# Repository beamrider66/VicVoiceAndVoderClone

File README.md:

# VVVC — Vic Voice and Voder Clone

Speech firmware for **ESP32 boards**, with always-on GPIO PWM audio and an
optional **ES8388 Audio-Kit 16-bit I2S DAC and speaker amplifier**. The same
SC-01 speech and startup tones feed both outputs without selecting a mode.
An absent codec does not prevent a normal DevKit from starting and speaking
through its PWM pin. GPIO audio needs an external filter and amplifier.

## One combined interface

The VIC serial connection accepts English text, compact SC-01 phoneme blocks,
VIC-Voice escape controls and VIC-Voder `SET TTY LO` / `SET TTY HI` baud commands
together. Text and phonemes can be mixed within a line. There is no mode to
select, and the former USB `-mode` commands have been removed.

Both the VIC connection and the USB console also accept commands to learn
phrases in numbered **RAM-only slots**, then replay them by number. Slots are
shared between the connections and disappear when the ESP32 reboots or resets.

All speech uses **one Votrax SC-01 approximation**. Startup defaults are
2400 baud with echo on; escape controls can switch echo off or back on. Settings
are held in RAM and reset restores the defaults. The USB console runs at
**115200 baud**. All dash commands work on **both connections**, including
`-demo`, `-tone`, `-phonemes`, `-help` and every learning command. Replies return
to the connection that sent the command. `-demo` is a one-shot test and
preserves the serial settings and learned slots.

The combined interface provides VIC-Voice-style controls and **SC-01 compact
phone numbering**, plus the basic text and
baud commands documented in the [VIC-Voder user's guide](https://www.geocities.ws/cbm/vic-voder/vic-voder-manual.pdf).
It does not implement the original SP0256 phone set or reproduce VIC-Voder's
Festival voice or Linux features. Combining the controls also means command
handling and echo defaults differ from the individual original products.

## End-user guide

The combined [user and VIC-20 wiring guide](output/pdf/VVVC_User_and_VIC20_Wiring_Guide_v2.pdf)
contains USB and VIC BASIC examples, learning commands, the Wizard of Wor loader
and all 75 phrase numbers. Its wiring section labels the viewing direction and
TOP for the computer port, cable mating face and wire/solder side. It remains a
review draft until the physical VIC connection and examples have been tested.

To regenerate it from the project folder:

```sh
python -m pip install -r tools/requirements-docs.txt
python tools/build_user_guide.py
```

## KiCad VIC user-port carrier (draft)

The repository also contains a first-pass [ESP32 user-port/audio carrier](hardware/VVVC_UserPort_Audio_WIP/README.md).
It is designed for a 38-pin ESP32 DevKitC/WROOM powered from USB, with a
dual-gang volume wheel for the shared 3.5 mm and RCA outputs, user-port edge
contacts, and enclosure standoff holes. The PCB is still a placement/netlist
draft: the exact audio-buffer and connector parts must be selected, routing
completed, and the enclosure checked before fabrication. The flashing guide
continues to cover firmware installation and serial setup; it does not present
this unfinished carrier as a production hardware option.

## Build and upload

On Windows, double-click [`build_and_flash.bat`](build_and_flash.bat) to build
and flash **COM3**. The window stays open to show the result. From a terminal:

```bat
build_and_flash.bat COM3
build_and_flash.bat COM7
build_and_flash.bat --build-only
```

Use the board's USB-to-UART port, and close the serial console first. The script
finds PlatformIO in its usual VS Code installation or on PATH, builds the
`esp32dev` environment, and uploads only if the build succeeds. It works from
any current directory. Flashing resets the board and clears learned RAM phrases;
run the Wizard loader again if needed. `--build-only` leaves the board alone.

Open this folder in VS Code with PlatformIO, or run:

```sh
pio run
pio run -t upload
pio device monitor
```

The default build environment is `esp32dev`. The Espressif32 platform is pinned
to `7.0.1`, the pinned build version. PlatformIO
automatically downloads Phil Schatzmann's `arduino-audio-driver` at **v0.1.3**,
the same codec library version used by the firmware. No filesystem image, Wi-Fi
configuration or separately downloaded speech library is required.

The available builds use 4 MB flash layouts and the board's USB-to-UART port:

| Environment | Chip family | PWM audio GPIO | VIC RX / TX | Codec output |
| --- | --- | --- | --- | --- |
| `esp32dev` | Original ESP32 (Audio-Kit or DevKit) | 22 | 18 / 5, UART2 | ES8388 if detected |
| `esp32c3` | ESP32-C3 | 4 | 6 / 7, UART1 | None |
| `esp32s2` | ESP32-S2 | 4 | 6 / 7, UART1 | None |
| `esp32s3` | ESP32-S3 | 4 | 6 / 7, UART1 | None |

For example, `pio run -e esp32c3 -t upload --upload-port COM7`. The batch file
continues to build the original ESP32 target. Each chip family needs its own
binary; PWM does not make one binary run on every ESP32. These four families
are build-checked with the pinned Arduino 2.0.17 toolchain. C2/C6/H2/P4 and
other families are not supported by these builds. Boards need at least 4 MB
flash and the chosen pins exposed and unused. Native USB-only boards need a
USB-to-UART adapter for the console with these profiles.

The PWM pin can be changed with `-DVVVC_PWM_PIN=number` in the environment's
`build_flags`. Preserve existing flags. Avoid flash, PSRAM, USB, boot-strapping,
UART, onboard peripheral and codec pins. The classic ESP32 build probes I2C
on GPIO33/32; keep these free even on a board without the codec. Do not press
any board button connected to an output. Check the specific board schematic.

If PlatformIO is not on your Windows PATH, its installed executable on this
machine can be invoked from PowerShell:

```powershell
& "$env:USERPROFILE\.platformio\penv\Scripts\pio.exe" run
& "$env:USERPROFILE\.platformio\penv\Scripts\pio.exe" run -t upload
& "$env:USERPROFILE\.platformio\penv\Scripts\pio.exe" device monitor
```

If several boards are connected, specify the appropriate `--upload-port COMx`
or monitor `--port COMx`. The application image is
`.pio/build/esp32dev/firmware.bin`; use PlatformIO upload to include the matching
bootloader and partition table.

## Browser installer

The installer is published at <https://beamrider66.github.io/VicVoiceAndVoderClone/>.
The public project repository holds firmware source on `main` and generated
website files on `gh-pages`. To rebuild and publish an update:

```powershell
powershell -File tools/publish_pages.ps1
```

GitHub Pages serves the root of the project's `gh-pages` branch over HTTPS.
The script requires Python, PlatformIO, Git and authenticated push access to
`beamrider66/VicVoiceAndVoderClone`. It builds locally and pushes the static files;
GitHub then deploys them automatically.

**Direct browser flashing requires HTTPS** (with a trusted certificate), or a
local server on `http://localhost`. The installer provides a ZIP download:
extract it, run `start-local.bat` with Python 3 installed, then open
`http://localhost:8765` in desktop Chrome or Edge.

Build the flashing site locally with:

```powershell
python tools/build_web.py
```

Omit `--publish` to generate only `build/web`. The script builds the current
firmware, merges the four flash images with DIO/40 MHz/4 MB settings, packages
ESP Web Tools 10.4.0 locally (verified against its npm SHA-512), and creates a
manifest, firmware checksum, guide and portable ZIP. No CDN is needed at runtime.
Publishing verifies copied files and retains older firmware images. Source page
files are in `web/`; generated files are ignored under `build/`.

The installer selects ESP32, C3, S2 or S3 firmware by chip family. It cannot
identify board wiring; users must check the pins above. Installation resets learned RAM
slots. This packaging process does not flash a connected device.

## Wiring

Connect the speaker to the Audio-Kit's **labelled speaker terminals**. The
headphone output is enabled as well. This uses the documented ES8388
Audio-Kit pin layout (`AudioKitEs8388V1` in the driver), including the required
master clock. The internal board connections are:

| Codec / amplifier connection | ESP32 pin |
| --- | --- |
| I2C SCL / SDA | GPIO 32 / 33 |
| I2S master clock (MCLK) | GPIO 0 |
| I2S bit clock (BCLK) | GPIO 27 |
| I2S word clock (LRCLK) | GPIO 25 |
| I2S data to ES8388 | GPIO 26 |
| Speaker amplifier enable | GPIO 21 |

Audio is **44.1 kHz, signed 16-bit stereo**, preserving the full SC-01 PCM
sample values and the documented Audio-Kit playback timing. Startup volume
is **48%**, adjustable with `audioVolumePercent` in
[`include/config.h`](include/config.h). GPIO25 carries the codec's digital
word clock, not analog audio. Audio-Kit buttons, SD and audio capture are unused.

### Always-on GPIO audio

GPIO22 on the original ESP32 (GPIO4 on the C3/S2/S3 profiles) carries the same
mono PCM as the codec, converted to **8-bit PWM with a 156.25 kHz carrier**.
It continues to run when no codec is installed; there is no fallback mode or
audio selection command. The codec retains the full 16-bit samples. PWM volume
is independent of the codec's 48% volume setting; adjust the external amplifier.
The two outputs have independent buffering/clocks and are not phase-aligned.

Use this starting circuit into a high-impedance amplifier input (47 kOhm or
greater). Values may need adjustment for the amplifier and desired bandwidth:

```text
PWM GPIO -- 1k --+-- 4.7k --+-- 1uF film -- amplifier audio input
                |         |
               22nF      4.7nF
                |         |
ESP32 GND ------+---------+-------------- amplifier signal ground
```

The RC stages suppress the PWM carrier; the film capacitor blocks the roughly
1.65 V idle DC level. Keep wires short and start at low amplifier volume. Use
an amplifier to drive the speaker: **do not connect a speaker or headphones
directly to the GPIO**, and do not connect the GPIO to the Audio-Kit speaker
terminals. The pin is a 0–3.3 V PWM signal, not a built-in DAC output or a
digital interface for an external DAC. During idle/after BREAK it rests at
50% duty; the startup beep, `-tone`, `-demo` and every speech source use it.

PWM uses LEDC low-speed channel/timer 0 and hardware timer 0. Its ring buffer
is in internal RAM; the sample ISR does no allocation or logging. The timer
rate is about 44101.43 samples/s (33 ppm above the nominal 44100 Hz). A stopped
sample timer times out rather than hanging speech. A failed audio backend is
disabled while the other continues. This new GPIO path has host and build
checks but still needs physical filter, waveform and simultaneous audio tests.
The existing PDF covers the earlier Audio-Kit wiring, not this new GPIO circuit.

The VIC interface retains its existing wiring:

| Connection | ESP32 pin |
| --- | --- |
| VIC user-port M, transmitted data, through a 5 V to 3.3 V divider | GPIO 18, UART2 RX |
| VIC user-port B and C, received data / receive interrupt | GPIO 5, UART2 TX, connected to both |
| VIC user-port A or N, signal ground | GND |

Use the documented interface circuitry. For the RX divider, the firmware
uses 10 kOhm from user-port M to GPIO 18 and 18 kOhm from GPIO 18 to ground.
Connect grounds and power the ESP32 separately over USB. This is a TTL
user-port connection, not the round IEC bus or a PC's RS-232 voltage interface.
Do not connect the VIC's 5 V transmit signal directly to the ESP32.

GPIO 18 and 5 are shared with Audio-Kit keys 5 and 6; leave those keys unused
when the VIC interface is connected. Startup echo, buffer sizes, phrase-bank
limits and the line timeout can also be changed in `include/config.h`.

## First test

After upload, open the USB console at 115200 baud with a newline terminator.
Startup plays the original **880 Hz then 440 Hz** audio test (300 ms each,
with a 100 ms gap) through PWM and any detected ES8388, then prints help. To check speech too, send:

```text
-demo
```

Expect 880 Hz and 440 Hz tones, then “HELLO WORLD. THIS IS VIC VOICE.” and
“GET READY.” The last phrase exercises direct phoneme synthesis separately
from English conversion. The console prints `Demo complete.` on success.
The demo checks the local speech/audio path; a VIC BASIC test checks the wiring
and UART separately.

If codec or I2S initialization fails, the console reports the error and skips
the startup tones. Check the board, then reset the ESP32. Learning and help
commands remain available, but playback reports failure while audio is
unavailable. Normal speech drains its final samples before returning; BREAK
clears queued audio immediately.

Commands accepted over USB or the VIC serial connection:

```text
HELLO WORLD
-phonemes G EH T R EH D Y PA1
-phonemes I0_AH I1_AH I2_AH I3_AH
-tone
-help
```

With VIC channel 1 already open at 2400 baud, the same commands can be sent with
`PRINT#1`, for example:

```basic
PRINT#1,"-DEMO"
PRINT#1,"-TONE"
PRINT#1,"-PHONEMES G EH T R EH D Y PA1"
PRINT#1,"-HELP"
```

Send one at a time and wait for completion. Demo and tone reply with
`Demo complete.` and `Tone complete.`; direct phonemes reply with
`OK PHONEMES`. Errors also return to the requesting connection. Replies use
ASCII and CR/LF. Disable VIC echo before parsing replies (see below), and
read `-help`/`-slots` output as it arrives: long replies can exceed the VIC's
small receive buffer. Explicit demo, tone and phoneme commands still play
audio with PSEND enabled. Unknown dash commands report an error on either port.

On the USB console, a leading `~`, PETSCII
pi (`0xDE` or `0xFF`) or UTF-8 pi selects **compact** Type 'N Talk bytes for that
USB line. Use `-phonemes` for readable SC-01 tokens. USB lines accept up to 253
bytes; longer lines are discarded with an error, rather than spoken partially.
USB commands run between utterances. There is no background demo loop.

## Learning and recalling phrases

There are **80 slots, numbered 1 through 80**, each holding up to **256 SC-01
phonemes**. Text is converted when learned; recall uses the saved phonemes
directly. Named phonemes retain `I0_` through `I3_` inflection prefixes. All
storage is normal RAM, using about 20 KB for the bank plus conversion workspace.
The firmware does not save phrases to flash or a filesystem.

Send these commands as complete CR- or LF-terminated lines on either port:

| Command | Action |
| --- | --- |
| `-learn 1 text HELLO WORLD` | Convert English and store it in slot 1, without speaking it |
| `-learn 2 phonemes G EH T R EH D Y PA1` | Store named SC-01 phonemes in slot 2 |
| `-learn 3 compact ~\{j~?` | Store compact codes for `G EH T PA1` in slot 3 |
| `-play 1` | Speak slot 1 |
| `-forget 1` | Delete slot 1 |
| `-slots` | List occupied slots and their phoneme counts |
| `-clear` | Delete every slot |

Commands and named phonemes are case-insensitive. Compact codes are
case-sensitive bytes, preserved exactly. In the compact example, `\` is one
literal backslash. A compact block must have an opening pi marker and a closing
`?`; its data bytes must all be `0x40` through `0x7F`. Use ASCII `~` or PETSCII pi
(`0xDE` / `0xFF`) on the VIC connection; the USB console also accepts UTF-8 pi.
The opening marker and closing `?` are not stored. Compact input uses inflection
zero; use named phonemes to specify inflection.

Relearning an occupied slot replaces it only after the complete new phrase
passes validation. Invalid or oversized input leaves the old phrase intact.
Text input is limited to 253 bytes before conversion, and the converted result
must fit in 256 phones. The USB line limit is 253 bytes **including the command**;
the VIC buffer accepts up to 768 bytes including the line terminator. The bank
limits can be changed with `phraseSlotCount` and `phrasePhoneLimit` in
`include/config.h`.

All dash commands require CR or LF. An unfinished VIC command is rejected at
the inactivity timeout or buffer limit; the remainder is discarded through
the next CR/LF. When a receive overflow occurs during playback, pending input
is discarded through the next terminator. This prevents a truncated learn
command from silently replacing a valid slot. Send one command and wait for
its reply before sending the next.

### Replies

Replies are ASCII, terminated by CR/LF, and sent to the connection that issued
the command. A successful learn, play or forget returns `OK n`, for example:

```text
OK 1
```

`-play` replies after playback completes. A BREAK/NUL interruption returns
`ERROR n PLAYBACK INTERRUPTED` and keeps the stored phrase. Empty slots, invalid
numbers and invalid content produce errors such as `ERROR 1 EMPTY SLOT`,
`ERROR SLOT MUST BE 1..80` or `ERROR 1 INVALID PHONEME`. Clear returns `OK CLEAR`.
A list reply looks like:

```text
SLOTS 2
SLOT 1 8
SLOT 2 8
END
```

`SLOTS` reports how many slots are occupied; each `SLOT` line gives the slot
number and phoneme count. An empty bank returns `SLOTS 0` followed by `END`.
The list reports stored phoneme counts, not the original English text.

VIC command replies are sent even when echo is off. For automated clients,
disable echo first with `ESC`, `0x14` and a carriage return, so echoed input
does not precede the replies. PSEND and CAPS settings do not alter learning
commands: text is learned with normal English pronunciation, and explicit
`-play` always produces speech. Both ports access the same bank, so a phrase
learned over USB can be recalled from the VIC, and vice versa.

To send the example commands from VIC BASIC, use the normal channel:

```basic
OPEN1,2,3,CHR$(10)
PRINT#1,"-LEARN 1 TEXT HELLO WORLD"
PRINT#1,"-PLAY 1"
CLOSE1
```

The ESP32's boot path clears every slot, including after the serial `ESC`,
`0x18` reset command. Resetting the VIC alone does not reset a separately
powered ESP32. Ordinary speech, baud changes and `-demo` preserve the bank.

## Loading the old Wizard of Wor phrases

[`tools/learn_wizard.py`](tools/learn_wizard.py) teaches **all 75 phrases** from
the old project's table, keeping the original phrase numbers and `I1_` / `I2_` /
`I3_` inflection tokens. The catalog is included in
[`tools/data/wizard_of_wor.json`](tools/data/wizard_of_wor.json); the old project
does not need to be installed beside VVVC. The phrases are host-side data and
are loaded into RAM through the ordinary `-learn` interface.

Upload the current 80-slot firmware, close the PlatformIO serial monitor, then
run from the project folder (replace `COM5` with the board's USB serial port):

```powershell
python -m pip install -r tools/requirements.txt
python tools/learn_wizard.py --port COM5
```

This fills slots **1 through 75**, replacing any phrases already in those
slots. Slots **76 through 80** remain available for other phrases. The script
waits for each `OK`, then verifies every loaded slot's phoneme count. It prints
the slot-to-phrase mapping and stops on errors. It does not play while learning.

Useful options:

```powershell
python tools/learn_wizard.py --list
python tools/learn_wizard.py --dry-run
python tools/learn_wizard.py --port COM5 --phrases 21 26 55 --play 21
```

`--phrases` loads only the specified original IDs, preserving their slot
numbers. `--dry-run` prints the exact learn commands without opening a port.
`--play 21` plays "Get ready, worrior." after loading and verification. Once
learned, send **`-play 21`** from either USB or the VIC connection to recall it;
all the other phrases work the same way. A bare number is still ordinary text.

The loader uses USB at 115200 baud and needs Python 3 and `pyserial`. On this
machine, PlatformIO's Python already includes `pyserial`:

```powershell
& "$env:USERPROFILE\.platformio\penv\Scripts\python.exe" tools/learn_wizard.py --port COM5
```

Run the loader again after an ESP32 reboot/reset. Some serial monitors reset
the ESP32 when opening their port, which also clears the learned bank; using
the VIC connection or the loader's `--play` option avoids reopening USB to test.

## VIC serial input

The default is **2400 baud, 8 data bits, no parity, one stop bit**, without
hardware flow control. A simple VIC BASIC test is:

```basic
10 OPEN1,2,3,CHR$(10)
20 PRINT#1,"HELLO WORLD"
30 CLOSE1
```

The application receive buffer is 768 bytes. Long text is split at word
boundaries for conversion. Pending input is processed after
four seconds of inactivity if the sender omitted a terminator. The VIC UART
continues receiving during speech; when its finite buffers fill, pending
input may be discarded. Pace large transmissions instead of continuously
streaming faster than the device can speak.

### Text, phonemes and escape controls

CR or LF processes a line. Echo is enabled initially. A pi marker
(`0xDE`, `0xFF`, or ASCII `~`) starts a compact SC-01 block within the text;
`?` ends it. Compact bytes `0x40` through `0x7F` select the 64 SC-01 phones.
The text before and after a phoneme block is spoken normally. All USB dash
commands, including `-phonemes`, `-demo`, `-tone` and `-help`, are also accepted
on the VIC connection. Command names and named phones accept ASCII or PETSCII
letters without changing compact phoneme bytes.

| Bytes | Action |
| --- | --- |
| `ESC`, `0x11` | PSEND on: send compact phonemes back instead of speaking |
| `ESC`, `0x12` | PSEND off |
| `ESC`, `0x13` | Echo on |
| `ESC`, `0x14` | Echo off |
| `ESC`, `0x15` | CAPS spelling on |
| `ESC`, `0x16` | CAPS spelling off |
| `ESC`, `0x17` | Disable the inactivity timer until reset |
| `ESC`, `0x18` | Restart the ESP32 |

The VVVC PETSCII letter conversion, cursor-sequence consumption and
single-device cascade responses are retained. There is no multi-device chain.
NUL stops the current phrase while preserving subsequently received input;
physical BREAK handling depends on the UART reporting it as NUL.

### Baud commands

These complete lines are always available on the VIC connection, including
when CAPS spelling or PSEND is enabled. They change the baud rate without
being spoken or returned as phonemes:

| Line | Action |
| --- | --- |
| `SET TTY LO` | Change the VIC UART to 1200 baud |
| `SET TTY HI` | Change it to 2400 baud |

Send the command at the **current** baud rate, then change the computer's baud
rate to match. On a VIC, use `CHR$(8)` when reopening the channel at 1200 baud,
and `CHR$(10)` at 2400. Pending echo is transmitted at the old baud rate before
the change. Baud commands preserve echo and the other settings; reset restores
2400 baud. Phoneme blocks and escape commands remain available at either speed.

## Source and checks

| Location | Purpose |
| --- | --- |
| `src/main.cpp` | Startup and USB line input |
| `src/serial_commands.cpp` | Common USB/VIC commands, demo, help and reply routing |
| `src/vic_serial.cpp` | Combined VIC text, phoneme, escape and baud interface |
| `src/phrase_bank.cpp` | Bounded RAM storage and validation of learned phrases |
| `src/phrase_commands.cpp` | Shared learn/play/list/delete commands and replies |
| `src/speech.cpp` | Shared SC-01 playback and interruption |
| `src/audio.cpp` | Fan-out to both outputs and startup/test tones |
| `src/audio_codec.cpp` | Optional ES8388/I2S 16-bit output and speaker amplifier |
| `src/audio_pwm.cpp`, `src/audio_pwm_hal.c` | Always-on buffered PWM and interrupt-safe duty updates |
| `lib/sc01/src/` | Portable speech engine, ROM tables and English conversion |
| `tools/learn_wizard.py`, `tools/data/` | USB loader and original Wizard of Wor phrase catalog |
| `test/`, `tools/check.py` | Host regression checks |

Run `python tools/check.py` with GCC/Clang available. The checks exercise
English conversion and bounds, all 64 compact phones, synthesis completion,
USB framing, mixed text/phonemes, VIC protocol controls, baud changes and demo
settings preservation. Shared-command checks compare both ports' output and
audio, including PETSCII, command errors, incomplete input, queued requests
and audio failures. Phrase-bank checks cover all 80 slots, size limits,
inflection, cross-port learning/replay, atomic replacement, interrupted or
truncated commands, deletion and boot-time clearing. DAC checks exercise full
16-bit sample preservation, stereo duplication, partial writes, startup tone
pitch/duration, silence, normal completion, BREAK and initialization/write
failures. These use host serial and codec/I2S adapters. Physical board testing
of the previous firmware also confirmed audible startup tones, the demo, USB text and phoneme speech,
loading all 75 Wizard phrases, and recalling a learned phrase. Electrical UART
timing and the VIC cable/BASIC examples still require the planned VIC test.
The shared demo/tone/help/phoneme commands have passed host checks. The revised
firmware was uploaded to COM3 on 2026-09-18 with flash hashes verified. USB help
confirmed the shared command set, the board reported `Demo complete.`, all 75
Wizard phrases were reloaded and verified, and slot 26 returned `OK 26` after
playback. The physical VIC serial connection remains untested.

The checks also learn all 75 Wizard phrases through the real firmware's USB
parser, compare their packed phonemes/inflections, and recall a loaded phrase
from the VIC port. Loader checks cover acknowledgements, verification, errors,
reset detection, old firmware rejection and selection of individual phrases.

English conversion uses a standalone, malloc-free **text-to-phoneme converter**
built on a 1,288-entry transcription
of the Votrax SC-01 Phonetic Dictionary, a small exact-word override table, the
public-domain NRL letter-to-sound rules and the NRL/Votrax IPA-to-SC-01 mapping
(with number expansion) and bounded output. See [`THIRD_PARTY.md`](THIRD_PARTY.md)
for provenance.

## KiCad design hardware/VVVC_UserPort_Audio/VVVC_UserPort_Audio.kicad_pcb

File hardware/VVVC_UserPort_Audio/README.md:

# VVVC User-Port Audio Carrier

KiCad 10 carrier PCB for the VVVC firmware. It plugs into the VIC-20 user
port, accepts a common 38-pin ESP32 DevKitC/WROOM development board, and breaks
out the audio and serial interface:

- 53 mm user-port insertion tongue with 24 contacts at 2.54 mm pitch. The
  contact geometry follows the open C64 diagnostic user-port board reference.
- ESP32 DevKitC/WROOM 38-pin socket headers. The USB connector remains exposed
  at the top edge for flashing and serial console use.
- GPIO22 PWM speech output on the original ESP32, through a two-stage filter.
- 3.5 mm stereo jack for the mixed line/headphone output.
- RCA input for VIC audio and RCA output for the mixed VIC + speech signal.
- Dual-gang 10 kOhm audio volume wheel after the buffer. It attenuates the
  headphone and RCA outputs together so the speech level can be matched to the
  VIC audio.
- Four 3.2 mm plated mounting holes on a 100 mm x 80 mm carrier outline for a
  future enclosure. Hole centers are (8,22), (92,22), (8,72), (92,72) mm.
- USB power through the ESP32 DevKit. Its USB 5 V pin feeds the carrier audio
  circuitry and its onboard regulator supplies 3.3 V. The VIC 5 V pin is
  deliberately left unconnected because the ESP32 can exceed the user-port's
  100 mA budget.
- This revision intentionally does not use or rectify the VIC's 9 VAC pins.
  Leave the two 9 VAC contacts unused and connect USB to the ESP32 board before
  using the carrier.

The audio section mixes the stereo RCA input with the filtered mono speech
signal, then sends the buffered stereo result through RV1 to both the RCA
output and the 3.5 mm jack. It is intended for powered speakers or a headphone-capable
amplifier. The ESP32 GPIO must never drive headphones directly. Fit the
optional NJM4556/OPA1678-class audio buffer and choose a headphone-safe supply
before connecting low-impedance headphones.

The enclosure should leave the ESP32 USB connector accessible at the top edge,
the 3.5 mm and RCA connectors accessible at the right edge, and a panel opening
for RV1's shaft/wheel beside those connectors. The 100 x 80 mm outline and the
four standoff centers in the netlist are the starting points for an enclosure;
check the actual connector bodies and shaft height against the parts purchased.

The generated board is a placement/netlist draft. It intentionally has no
copper routing because the final ESP32 header, audio buffer package, and jack
footprints must be confirmed against the parts being purchased. Open the board
in PCB Editor, route each highlighted net, run DRC, and check the 3-D view and
the physical user-port fit before ordering.

## User-port signals

The firmware interface uses M -> ESP32 GPIO18 (RX) through the 10 kOhm / 18 kOhm
divider, and ESP32 GPIO5 (TX) -> B and C. A and N are signal ground. The card
does not use the VIC 5 V or 9 VAC rails to power the ESP32; USB power enters
through the DevKit's 5 V header pin. The edge labels are
printed on the silkscreen. They are read from the component side with the
insertion tongue pointing away from you; verify this orientation against the
VIC service manual before inserting the card so the connector is not mirrored.

The populated user-port contacts are:

| Contact | Function |
| --- | --- |
| A, N, 1, 12 | GND |
| B, C | VIC transmit to ESP32 GPIO5 |
| M | VIC receive to ESP32 GPIO18 via the divider |
| 2 | Left open; VIC +5 V is not used |
| 10, 11 | Left open; VIC 9 VAC is not used |

All other contacts are left open for future expansion. The silkscreen is a
component-side aid, not a substitute for checking the mating connector's pin-1
mark and the board outline.

## Files

- `VVVC_UserPort_Audio.kicad_pcb` - PCB layout and footprints.
- `VVVC_UserPort_Audio.netlist.csv` - connector, signal and assembly notes.
- `generate_pcb.py` - deterministic generator for the board file.

This is an engineering first revision. Verify the physical user-port fit,
ESP32 board variant, jack footprints, audio gain and headphone safety with a
prototype before ordering a batch. Run KiCad's DRC after opening the board and
complete routing of any nets marked as unrouted.

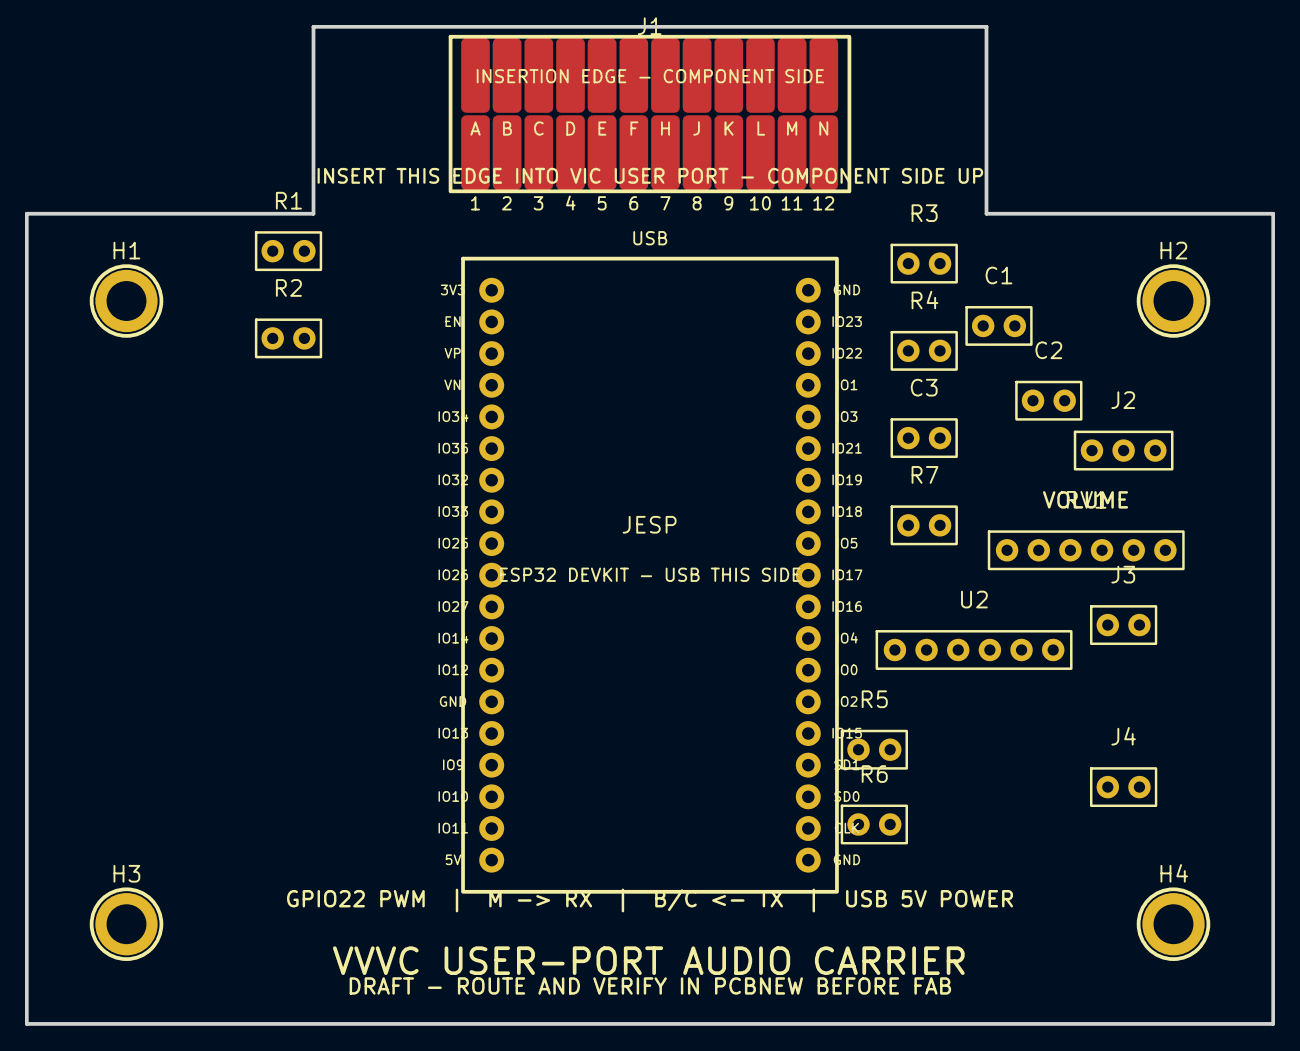
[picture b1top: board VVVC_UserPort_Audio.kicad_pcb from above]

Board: 2 copper layers, 100.0 x 80.0 mm, 21 parts (0 on the bottom side), 16 nets, no tracks yet.

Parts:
C1: 22nF; CAP_PWM_1
C2: 4.7nF; CAP_PWM_2
C3: 1uF FILM; CAP_PWM_DC
H1, H2, H3, H4: STANDOFF; MOUNT_HOLE_3V2
J1: VIC-20 USER PORT; VIC_USER_PORT_EDGE
J2: 3.5mm TRS; HEADPHONE
J3: RCA IN L/R; RCA_INPUT
J4: RCA OUT L/R; RCA_OUTPUT
JESP: ESP32-DEVKITC-32 / WROOM; ESP32_DEVKITC_38
R1: 10k; RES_RX_TOP
R2: 18k; RES_RX_BOTTOM
R3: 1k; RES_PWM_SERIES
R4: 4.7k; RES_PWM_FILTER
R5: 10k; MIX_IN_L
R6: 10k; MIX_IN_R
R7: 10k; MIX_SPEECH_R
RV1: DUAL 10k AUDIO VOLUME; VOLUME_DUAL_GANG
U2: NJM4556D / OPA1678; AUDIO_BUFFER

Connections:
+5V_USB: JESP.19, U2.5
AUDIO_IN_L: J3.1, R5.1
AUDIO_IN_R: J3.2, R6.1
BUF_L: RV1.1, U2.3
BUF_R: RV1.4, U2.4
GND: C1.2, C2.2, J1.1, J1.12, J1.A, J1.N, J2.3, JESP.14, JESP.20, JESP.38, R2.2, RV1.3, RV1.6, U2.6
MIX_L: C3.2, R5.2, U2.1
MIX_R: R6.2, R7.2, U2.2
PWM_AUDIO: JESP.22, R3.1
PWM_F1: C1.1, R3.2, R4.1
PWM_F2: C2.1, C3.1, R4.2, R7.1
RX_DIV: R1.2, R2.1
VIC_RX: J1.M, JESP.27, R1.1
VIC_TX: J1.B, J1.C, JESP.28
VOL_L: J2.1, J4.1, RV1.2
VOL_R: J2.2, J4.2, RV1.5
